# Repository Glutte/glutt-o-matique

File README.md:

Glutt-o-matique
===============

La nouvelle logique de la Glutte voit le jour ici.

On va utiliser un stm32f4-discovery. La collaboration
est gérée à l'aide d'un
[Trello](https://trello.com/b/NSvh8v81),
qui sert aussi d'aide-mémoire.

[La Glutte](http://www.glutte.ch)

L'essence de la glutt-o-matique
-------------------------------

Notre but  
est que la glutte  
fasse des tût-tûts.

Pour faire écho  
des beaux QSO  
depuis là-haut.

Donner comme retour  
entre chaque tour  
une lettre nuit et jour

Économiser l'energie  
pour la longue vie  
de la batterie.

Tout en annoncant  
le beau temps  
régulièrement.

Structure
---------

.

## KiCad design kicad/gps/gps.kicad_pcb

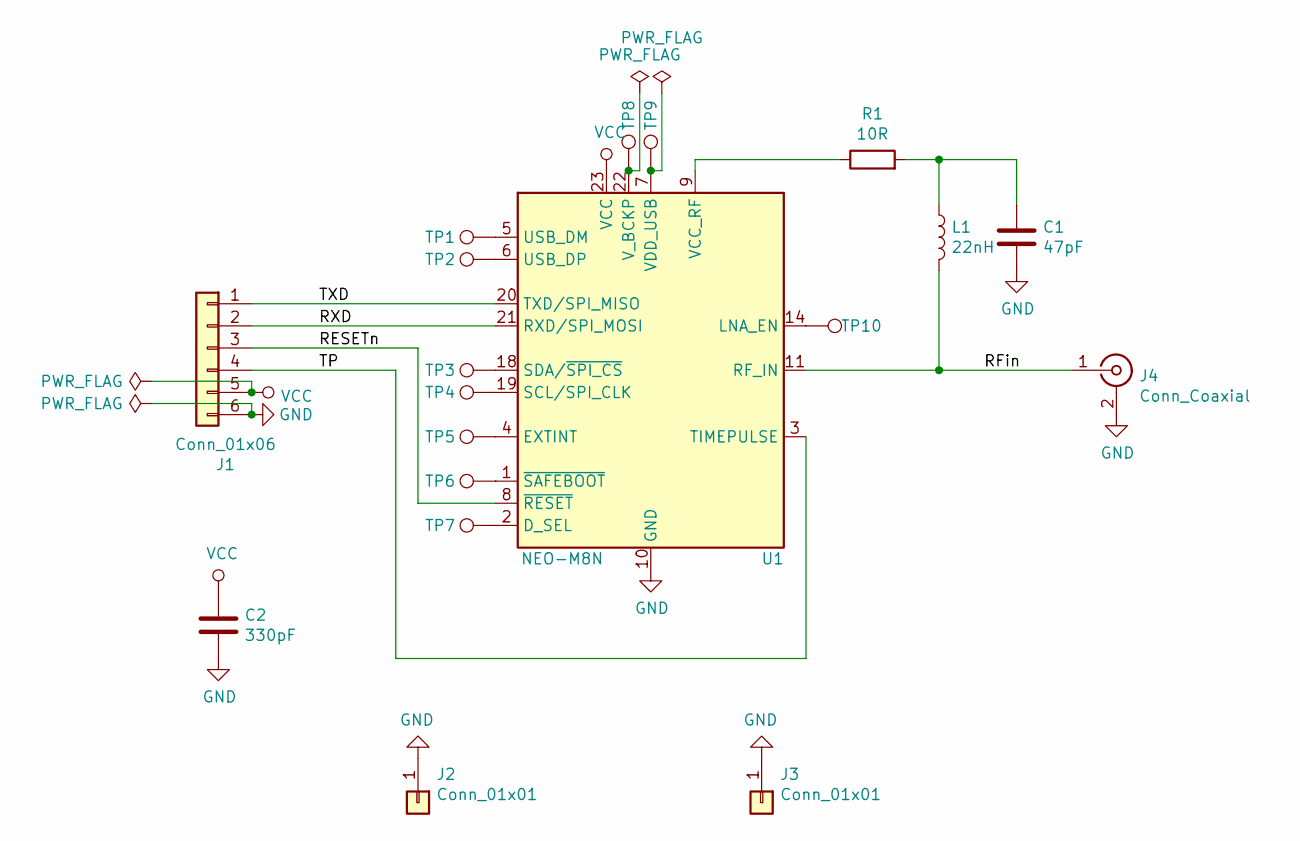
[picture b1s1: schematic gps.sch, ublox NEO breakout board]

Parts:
C1: 47pF; C_0603_1608Metric_Pad1.05x0.95mm_HandSolder
C2: 330pF; C_0805_2012Metric_Pad1.15x1.40mm_HandSolder
J1: Conn_01x06; PinHeader_1x06_P2.54mm_Vertical
J2, J3: Conn_01x01; PinHeader_1x01_P2.54mm_Vertical
J4: Conn_Coaxial; SMA_Samtec_SMA-J-P-H-ST-EM1_EdgeMount
L1: 22nH; L_0603_1608Metric_Pad1.05x0.95mm_HandSolder
R1: 10R; R_0603_1608Metric_Pad1.05x0.95mm_HandSolder
TP1: DM; TestPoint_Pad_1.0x1.0mm
TP2: DP; TestPoint_Pad_1.0x1.0mm
TP3: SDA; TestPoint_Pad_1.0x1.0mm
TP4: SCL; TestPoint_Pad_1.0x1.0mm
TP5: EXTINT; TestPoint_Pad_1.0x1.0mm
TP6: SB; TestPoint_Pad_1.0x1.0mm
TP7: DSEL; TestPoint_Pad_1.0x1.0mm
TP8: VBKP; TestPoint_Pad_1.0x1.0mm
TP9: VUSB; TestPoint_Pad_1.0x1.0mm
TP10: LNA; TestPoint_Pad_1.0x1.0mm
U1: NEO-M8N; ublox_NEO

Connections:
/RESETn: J1.3, U1.8 (~RESET)
/RFin: J4.1 (In), L1.2, U1.11 (RF_IN)
/RXD: J1.2, U1.21 (RXD/SPI_MOSI)
/TP: J1.4, U1.3 (TIMEPULSE)
/TXD: J1.1, U1.20 (TXD/SPI_MISO)
GND: C1.2, C2.2, J1.6, J2.1, J3.1, J4.2 (Ext), U1.10 (GND), U1.12 (GND), U1.13 (GND), U1.24 (GND)
unnamed: C1.1, L1.1, R1.2
unnamed: R1.1, U1.9 (VCC_RF)
unnamed: TP1.1, U1.5 (USB_DM)
unnamed: TP2.1, U1.6 (USB_DP)
unnamed: TP3.1, U1.18 (SDA/~SPI_CS)
unnamed: TP4.1, U1.19 (SCL/SPI_CLK)
unnamed: TP5.1, U1.4 (EXTINT)
unnamed: TP6.1, U1.1 (~SAFEBOOT)
unnamed: TP7.1, U1.2 (D_SEL)
unnamed: TP8.1, U1.22 (V_BCKP)
unnamed: TP9.1, U1.7 (VDD_USB)
unnamed: TP10.1, U1.14 (LNA_EN)
VCC: C2.1, J1.5, U1.23 (VCC)

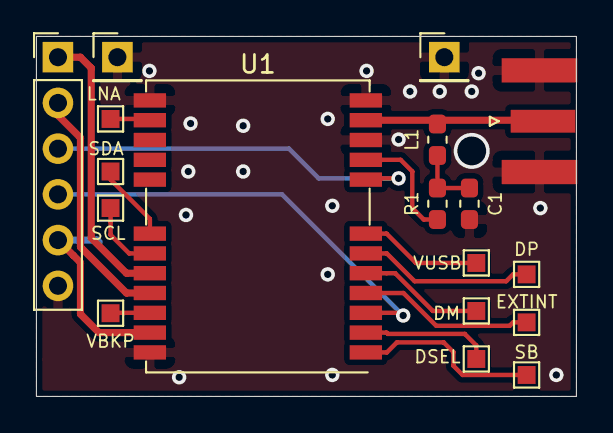
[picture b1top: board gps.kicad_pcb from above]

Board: 2 copper layers, 30.0 x 20.0 mm, 19 parts (1 on the bottom side), 19 nets.

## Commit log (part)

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2015-11-02 Add schematics
2015-12-03 add fsm definitions
2015-12-03 Add test1 example
2015-12-03 Set timestamp for first state
2015-12-03 Add README and doc
2015-12-06 README line breaks
2015-12-06 Reorder README
2015-12-06 Add CW code
2015-12-06 Basic gitignore
2015-12-06 Fix interrupt prio, add tone test
2015-12-07 Some cw fixes
2015-12-07 Move CW generation into a task
2015-12-07 Reduce CW clicks
2015-12-09 Add arm_sin_f32.c
2015-12-09 Make deploy dependant of ELF to autorebuild, reset and run cpu then exit
2015-12-09 Add trello to README
2015-12-09 Temperature measurements
2015-12-12 Add external pins to exercise FSM, timestamp and random_bool
2015-12-12 Ensure tm_trigger only does a single pulse
2015-12-19 Add GPS routine and UBX parser
2015-12-19 Fix I2C for GPS, needs timeout handling
2015-12-20 Properly reset I2C bus in case of error
2015-12-20 Give names to board leds
2015-12-20 Fix I2C SW reset
2015-12-20 Increase stack size for gps monit task
2015-12-20 Don't break FSM
2015-12-28 GPS: Replace UBX over I2C to NMEA over UART
2015-12-28 Correct GPS fix timeout handling
2015-12-28 Add dayofweek function
2015-12-28 Add PSK31 code and arm_cos_f32
2015-12-28 Enable makefile optimisations
2016-01-02 Change CW queue to contain text only, not on/off data
2016-01-02 Combine CW and PSK31 code
2016-01-03 Ugly-fix state machine diagram
2016-01-03 fsm: remove arrow from balise to OPEN2
2016-01-06 Add qucs sim for level shifter
2016-01-06 Update comments on GPS connection
2016-01-11 Clarify PIO usage and add TX_n OD output
2016-01-12 Change TX_n to TX
2016-01-17 perfboard: DB25 connector and inverting level shifter
2016-01-17 Perfboard: add mini-jack connector
2016-01-21 Distinguish pullup and nonpullup in PIO
2016-01-21 Initialise USART1 for PC debug
2016-01-22 Update FreeRTOS
2016-01-22 Add missing hardfault.s file
2016-01-24 Move debug UART to USART2, audio broken
2016-01-24 Fix vc.h generation
2016-01-24 Enable Tickless IDLE
2016-01-24 Fix vc.h order and ignore it
2016-01-24 Use GPIO functions in audio driver
2016-01-24 Enable Watchdog to 2 seconds
2016-01-25 Perfboard: move stm32, add MAX232
2016-01-26 Clean up state machine diagram
2016-01-26 Update PIO usage for new board
2016-01-26 PIO changes for perfboard
2016-02-02 Try to access DS18B20 on PA1
2016-02-02 Update perfboard drawing
2016-02-02 Make things on schematic smaller
2016-02-04 Add DCDC to schematic and perfboard
2016-02-04 Add LM324 to perfboard, update schematic
2016-02-07 Add power bus to perfboard
2016-02-07 Change all beziers to straight segments
2016-02-21 Reorder DB25 pin header
2016-03-15 Move some resistors
2016-03-15 Fix base board size
2016-03-15 Move MAX232 by one
2016-03-15 Move big header up by two
2016-04-10 Fix TX ON connections
2016-04-10 Change resistor orientation next to 2N2222
2016-04-10 Move MOD ON 2N2222
2016-04-10 Move MAX232
2016-04-17 Add usart_test with ds18b20 test
2016-04-17 fsm: disable USART2 RX
2016-04-17 fsm: Modify Makefile build dependencies
2016-04-17 Remove symlink src/fsm/ds18b20
2016-04-17 Add additional usart debugging
2016-04-17 Conditionnally initialise input pins w/o pullup
2016-04-18 Temperature
2016-05-06 Add pio_test subfolder
2016-05-14 Schematic: 22k instead of 20k divider
2016-05-14 Schematic: Update date
2016-05-29 Implement DST calculation
2016-05-29 Add start_tm ack signal
2016-05-30 Fix DB25 numbering
2016-05-30 Add more USART debug prints
2016-05-31 Simuator - Work in progress
2016-06-02 Simulator: UART, Leds, begining of GPS
2016-06-03 Working GPS simulator
2016-06-03 Simulator: GPS, Audio, CW
2016-06-05 Simulator: Input, outputs and FSM
2016-06-05 Fix timestamp and fsm date
2016-06-05 Remove pio_test project
2016-06-05 Remove usart_test
2016-06-05 Fix includes, add headers, add CW usart print
2016-06-05 Add bsp and FreeRTOS links
2016-06-05 Makefile: fix clean that deleted an .s file by accident
2016-06-05 Add missing hardfault.s
2016-06-05 Add licence headers
2016-06-05 Fix USART concurrency, create common usart object
2016-06-05 sim: Disable default GPS enabled
2016-06-05 Simulator: autoscroll
2016-06-05 Make object for common/Audio
2016-06-05 Make object for common/Core/common.c
2016-06-05 Make objects for common/ leds temperature
2016-06-05 Create bin folder automatically
2016-06-05 Change FAX signal polarity
2016-06-05 Fix GND on perfboard DB25
2016-06-05 Fix warnings
2016-06-05 "Fix" warnings
2016-06-06 Fix warnings, add more warnings flags, normalize makefiles
2016-06-06 Internal ts test
2016-06-07 Keep audio always on
2016-06-07 Never turn off audio
2016-06-11 i2c: prefer pdMS_TO_TICKS macro
2016-06-11 Rework i2c lockup handling
2016-06-11 trigger fault on task overflow
2016-06-11 Merge test and launcher tasks
    This saves some stack space
2016-06-12 Assign pins to analog inputs
2016-06-12 Add analog readout code for supply monitoring
2016-06-12 fix variable name and remove useless sqrtf call
2016-06-12 Improve supply voltage measurement, WIP
2016-06-12 Transmit voltage and temperature in beacons
2016-06-12 Update schematic and layout
2016-06-12 Add missing analog.c
2016-06-12 Add input voltage
2016-06-13 Update SECOURS on schematic and perfboard
2016-06-14 Generation of derived time
2016-06-14 Try to fix truncatered CW
2016-06-14 Better BASILE_COURTE -> OPEN
2016-06-15 Better SHORT_BEACON triggering
2016-06-15 Some comments
2016-06-16 Create backside connections document
2016-06-20 Assign GPS EPPS output in doc
2016-06-23 Update schematics and perfboard
    Add audio filter, Correct SWR measurement, Zener voltages, GPS EPPS output,
    Cosmetics
2016-06-24 Fix opamp connection on schematic
2016-06-24 Add code to read SWR analog voltages
2016-06-25 Added new GPS led
2016-07-10 Add GPS SMA connector to back plate
2016-07-10 Add REPLIE inverter and voltage shifter
2016-07-10 Add reflected power handling with fixed threshold
2016-07-13 Add sticker.svg
2016-07-14 Update schematic, make V-1wire fat
2016-07-17 Update FSM document
    - Add QSO to ECOUTE transition
    - Distinguish BALISE and BALISE_OPEN
2016-07-17 Add CW pre/postdelay to fsm
2016-07-18 Refactor fsm timing code
2016-07-18 Fix ATTENTE, require additional timing check
2016-07-18 Change minimum QSO length for LETTER to 3s
    It feels more natural, 5s is a bit longish.
2016-08-20 Remove temperature print on button press
2016-08-29 Remove RAW Meas debug printf
2016-09-03 Add more debugging every 30s
2016-09-03 Make letter G same speed as other
2016-09-04 Fix equals sign in cw
2016-09-04 Remove useless tm_trigger setting
2016-09-04 Debounce SQ, D and U signals
2016-09-04 Add D and U debugging
2016-09-04 Rework balise trigger and fix ECOUTE lockup
2016-09-04 Add more logging for even time
2016-09-09 Reset GPS on startup
2016-09-09 Parse and print GPS GNTXT messages
2016-09-09 Parse GNGGA and print number of SV
2016-09-10 Print REPLIE signal
2016-09-12 Minor short beacon counter simplification
2016-09-12 Reset short beacon counter on long beacon TX
2016-09-12 Give name to codec reset pin
2016-09-12 Remove unused audio functions
2016-09-12 Add timeout for cw_audio_queue push and new fault
2016-09-15 Press bouton bleu for balise
2016-09-15 Increase cw postdelay and add it also to 73
2016-09-15 Fix only_zero_in_audio_buffer condition
2016-09-15 Add debug for audio. Fix green blinking led
2016-09-18 Move v_ref to toplevel of analog_input
2016-09-18 Add ADC1 timeout and corresponding new fault source
2016-09-18 Remove inapplicable TODO, it's correct
2016-09-18 Remove TODO, schematic shows pin is never floating
2016-09-21 Update ECOUTE transitions in fsm doc
2016-09-21 Update resistors on V1wire perfboard
2016-09-26 Suspend scheduler while waiting for ADC measurement
2016-09-26 Improve vc.c generation
2016-10-20 Unify representation of tm_year
2016-10-20 Restart QSO duration counter once end text sent
2016-10-21 Update statemachine diagram
2016-12-10 Reduce delay after end of balise
2016-12-17 Initialise struct tm in gps_monit_task
2016-12-20 Avoid letter delay if QSO duration was between 3 and 5 sec
2017-04-30 Increate delay after locator
2017-04-30 Allow to open the relay with SQ using fax mode
2018-05-09 Fix analog_supply_too_low() comment
2018-05-09 Add BUG_1750_BROKEN workaround
2018-05-10 Base with a working implementation on the simulator for software 1750 detection
2018-06-17 Add tone-test-sim
2018-06-19 Widen frequency range of tone test
2018-06-19 Fix tone test generation
2019-01-27 Corrections Synoptique
2019-01-28 Update Synoptique, add Synoptique 2016
2019-03-01 Add new FAX and 1750 interconnect board
2019-03-01 Remap PIOs in pio.txt, schematic and layout
2019-03-02 layout: connect new outputs
2019-03-02 rename fsm input variables
2019-03-02 Make 1750 detector work in simulator FSM
2019-04-11 Add some 1750 detection code to glutt-o-logic
2019-04-11 Document openocd + gdb
2019-04-11 Improve FM TX GRC
2019-04-11 Rework tone detector
    - Send buffer pointers from ISR to userspace
    - Use ADC interrupt to fetch data, not TIM6
    - Increase size of buffer and do double-buffering
    - Implement DTMF detectors
    - Compare relative results instead of using absolute thresholds
    - Add an IIR averaging filter on the results
2019-04-11 Reorder audio output NVIC settings
2019-04-13 Enable FAX mode when DTMF sequence detected
2019-04-14 Add task cpu usage printout code, disabled by default
2019-04-14 Switch to 16kHz audio
2019-04-19 tone: do Q1 and Q2 calculation inside IRQ
2019-04-19 Upgrade FreeRTOS to 10.2.0
2019-04-19 Disable Tones debugging
2019-04-22 Add a bit of delay on the 1750 detector
2019-05-03 Handle 1750 front button
2019-05-03 Minor schematic and board changes
2019-05-06 Move spec and some doc from trello to doc/
2019-05-10 Fix SQ2 output to 0
2019-05-10 Implement 5s 1750 to disable FAX
2019-05-10 Increase DTMF interval to 2.5s
2019-05-10 Move PA signal on fax_1750_interconnect schematic
2019-05-10 Remove TODO warnings
2019-05-10 Fix tone LED in code and schematics
2019-06-23 Show ALIM and TEMP independently of GPS time
    This avoids the bot complaining about no UART messages after a startup where GNSS never gets a fix
2019-06-24 Add Kicad project for a NEO gps breakout board
2019-06-24 Remove TODOs for SQ2 and 1750 outputs
2019-06-24 Send beacons even if GPS never starts giving time
2019-06-28 Fix FSM deadlock in FSM_BALISE_COURTE_OPEN
    When cw_psk31_done and sq occur simultaneously while inside FSM_BALISE_COURTE
2019-06-29 Change common/ folder structure
2019-07-01 Fix printf warnings
2019-07-05 stats: add GNSS SV and QRP percentage. Also use derived time
2019-07-05 Adapt QRP QRO voltage thresholds
2019-07-05 Suppress warning in cw.c
2019-07-07 Remove fprinf from Core/main.c
2019-07-07 Also send PSK125 in special balise
2019-07-09 Stats: fix number of GNSS SVs used
2019-07-18 Add PSK125 decoder script
2019-09-03 Fix uptime calculation after 25days
2019-12-07 Avoid using functions requiring locale support
    isdigit() and similar from ctype.h require this. Apparently
    this is not supported in the same way anymore on ARM.
2019-12-08 Replace DTMF 0,7,star by 1,7,star
2019-12-08 Make 1750 react in 300ms instead of 500ms
2020-04-20 Add BMP085 to the temperature sw project
2020-04-20 Mention gr-radioteletype in README
2020-04-26 Add missing files
2020-04-26 Enable STM32 USART2 RX
2020-05-03 Stats: capa in Ah
2020-08-11 Set QRP on high SWR before TX off
2020-10-03 Add bat capacity in beacons
2020-10-03 Fix TEMP printout
2020-10-25 Add EOL SK message when wind gen breaker is open
2020-10-25 Add Disjoncteur eolienne to stats
2020-10-30 Handle batterycharge_wind_disconnected() returning -1
2020-10-30 Handle batterycharge_too_low() returning -1 properly
2020-10-30 Reduce 1750 threshold to 250
2020-11-16 GUI: adapt panel sizes
2020-11-16 Flush audio at end of CW/PSK
2020-11-16 FSM: Trigger CW only once in BALISE_LONGUE
2020-11-17 SSTV: use nanoseconds for duration, change test pattern
2021-03-25 Port analyse_capture.py to GNURadio 3.8
2023-12-31 Refactor CW call into #define
2023-12-31 Change CW call to HB90G for the entire year 2024
